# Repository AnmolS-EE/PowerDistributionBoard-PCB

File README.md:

# PowerDistributionBoard-PCB
A high-efficiency power distribution board (PDB) designed to convert a single DC input (24V/10A) into multiple regulated rails for laboratory and personal device charging. This project has a custom-designed buck converter stage, individual USB Power Delivery (PD) controllers, and an ESP32 for real-time telemetry and monitoring. It will be designed on a 4-layer PCB board designed in KiCad.
## Schematic
V1.0 of the schematic is complete. As seen by the image below, it is neatly organized into the four main compartments: MCU(Microcontroller), Power management, Power analysis and USB ports.

## PCB Design
The PCB design and layout is currently a work in progress. Schematic and simulations are being thoroughly verified first. 

## Simulations
### 24V to 5V Step-Down Buck Converter
**Objective:** Step down the 24V main system power to a highly stable 5V rail.

**Simulation Note (XL4016 vs. LT1074):** 
The XL4016 used in the KiCad schematic doesn’t have a public SPICE model, so I used the Analog Devices LT1074 to simulate the circuit and verify the LC filter design and transient behavior.
 
 Note: The feedback resistors in the simulation (1kΩ / 1.26kΩ) were chosen to match the LT1074’s 2.21V reference. On the actual PCB, I’m using (1kΩ / 3kΩ) based on the XL4016’s 1.25V reference.

**Simulation & Stress Test:**
I tested the regulator under a continuous 2.5A load (modeled as 2Ω) to check how the 47µH inductor and 470µF output capacitors perform. The capacitors were modeled with a realistic ESR of 50mΩ.

**1. Transient Startup & Output Ripple:**

The system ramps up to 5V in less than 2ms. Steady-state analysis at full load shows a peak-to-peak voltage ripple of roughly 40mV (under 1%), confirming the power delivery is quite clean.

### 3.3V Logic Rail
**Objective:** Provide a stable power rail for the ESP32-S3-WROOM-1 microcontroller and I2C peripherals using the AMS1117-3.3. 

**Simulation & Stress Test:**
To verify the stability of the AMS1117-3.3V LDO regulator, the circuit was simulated in LTspice. I applied a 5-ohm load to force a continuous 660mA draw which is double the worst-case scenario in real life.

**Conclusion:**
As shown in the transient analysis above, the input of 5V (blue line) is converted into 3.3V (green line). The total load of the 3.3V rail (red line) remains perfectly flat under a 660mA continuous load with no voltage drop. The schematic confirms the test parameters, proving the power delivery is efficient enough to power the microcontroller and other perpherals.

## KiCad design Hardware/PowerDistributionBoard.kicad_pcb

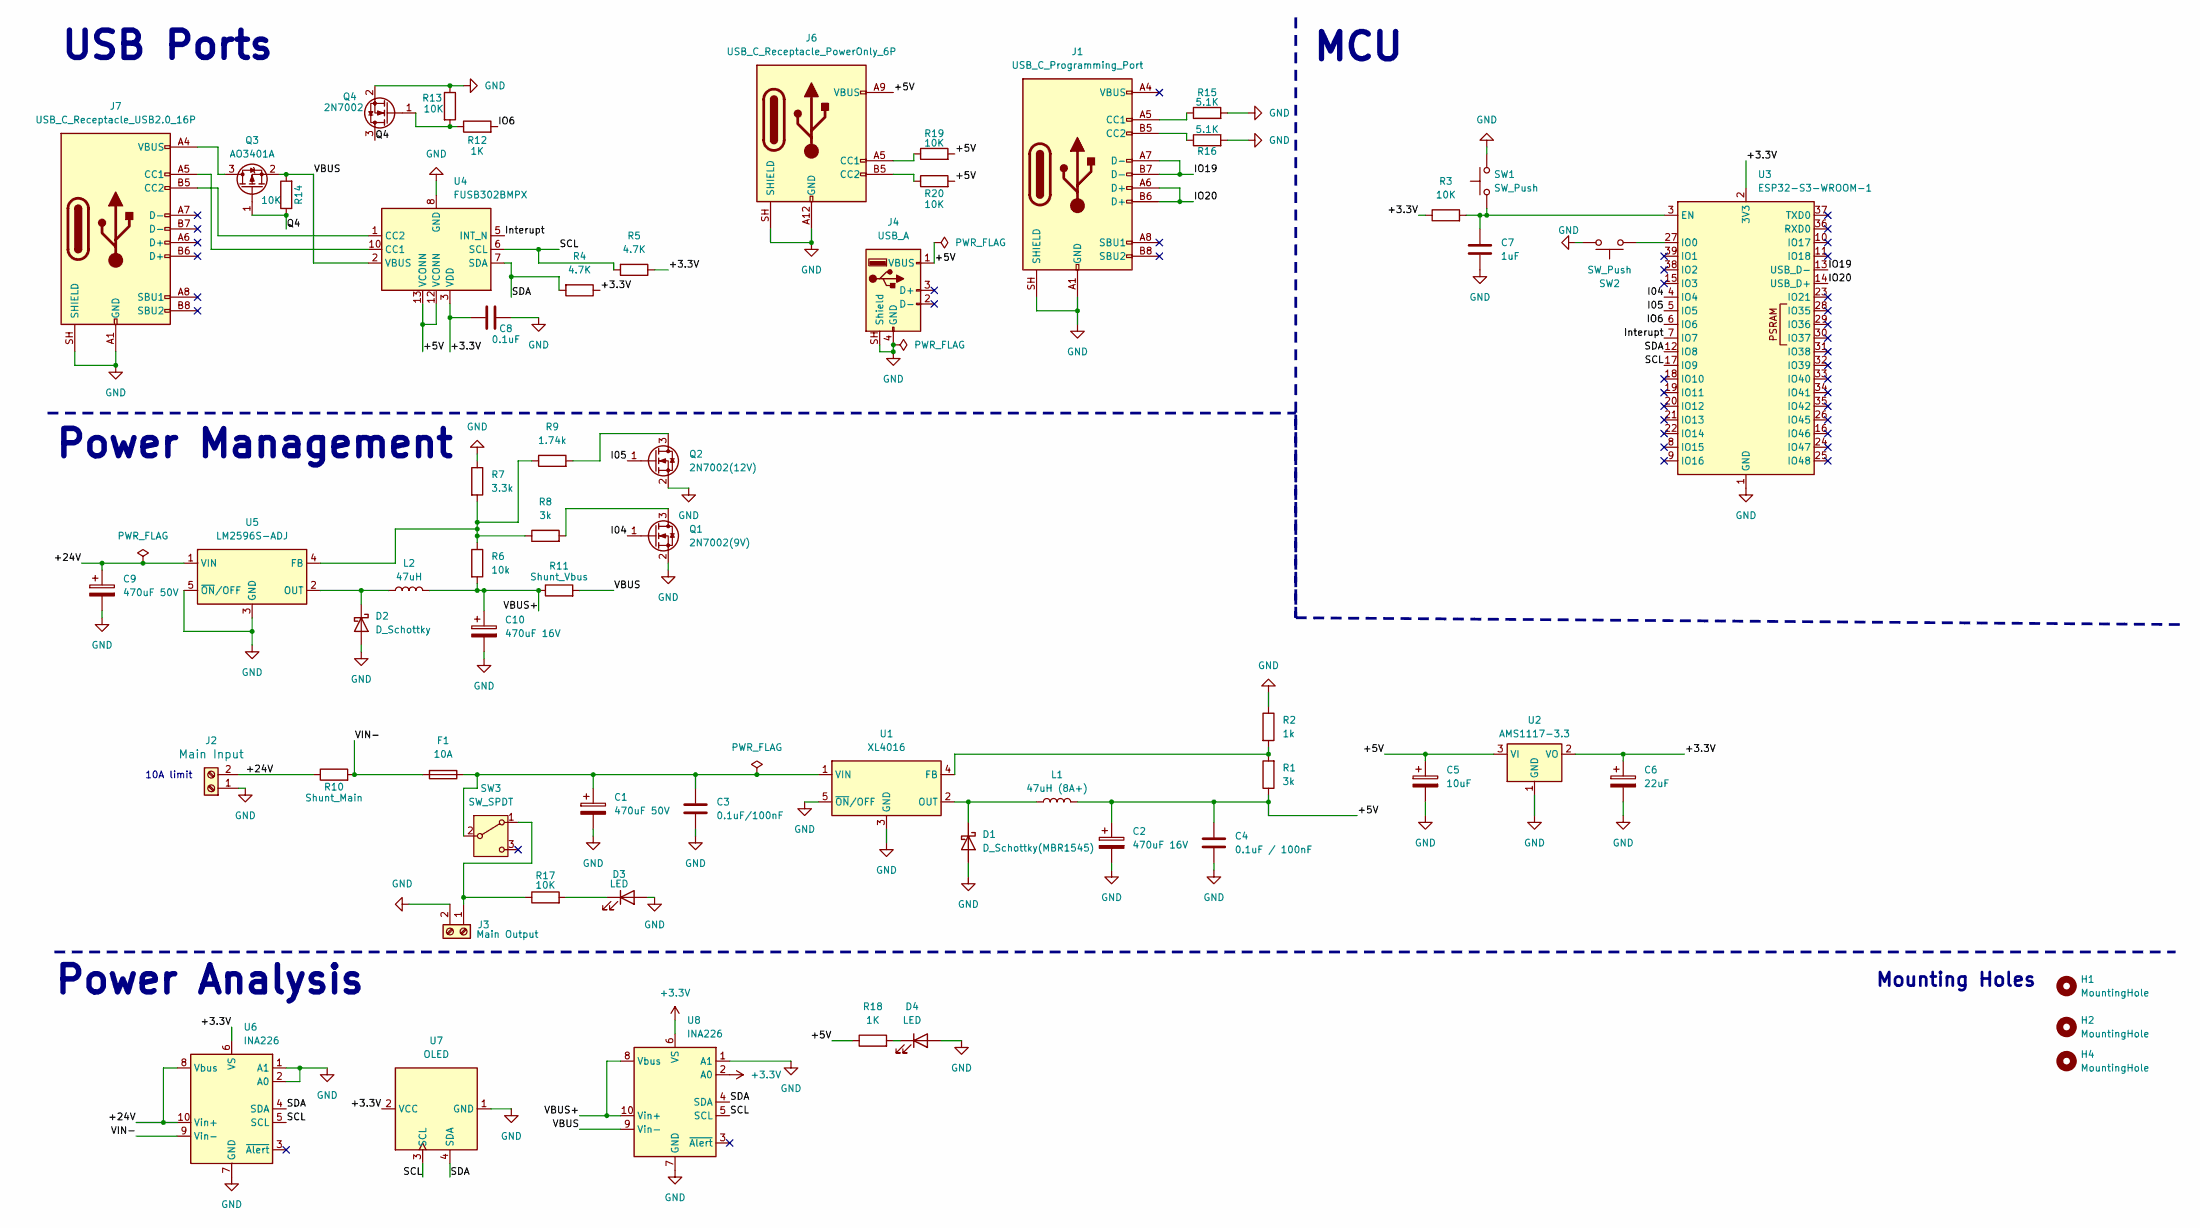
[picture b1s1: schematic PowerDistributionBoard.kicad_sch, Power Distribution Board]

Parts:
C1, C9: 470uF 50V; CP_Radial_D10.0mm_P5.00mm
C2, C10: 470uF 16V; CP_Radial_D8.0mm_P3.50mm
C3: 0.1uF/100nF; C_0805_2012Metric_Pad1.18x1.45mm_HandSolder
C4: 0.1uF / 100nF; C_0805_2012Metric_Pad1.18x1.45mm_HandSolder
C5: 10uF; CP_Radial_D5.0mm_P2.00mm
C6: 22uF; CP_Radial_D5.0mm_P2.00mm
C7: 1uF; C_0805_2012Metric_Pad1.18x1.45mm_HandSolder
C8: 0.1uF; C_0805_2012Metric_Pad1.18x1.45mm_HandSolder
D1: D_Schottky(MBR1545); TO-220-2_Vertical
D2: D_Schottky; D_SMC_Handsoldering
D3, D4: LED; LED_D3.0mm
F1: 10A; Fuseholder_Cylinder-5x20mm_Schurter_0031_8201_Horizontal_Op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
H1, H2, H4: MountingHole; MountingHole_3.2mm_M3
J1: USB_C_Programming_Port; USB_C_Receptacle_HRO_TYPE-C-31-M-12
J2: Main Input; TerminalBlock_Phoenix_MKDS-1,5-2-5.08_1x02_P5.08mm_Horizont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
J3: Main Output; TerminalBlock_Phoenix_MKDS-1,5-2-5.08_1x02_P5.08mm_Horizont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
J4: USB_A; USB_A_Molex_67643_Horizontal
J6: USB_C_Receptacle_PowerOnly_6P; USB_C_Receptacle_GCT_USB4125-xx-x_6P_TopMnt_Horizontal
J7: USB_C_Receptacle_USB2.0_16P; USB_C_Receptacle_HRO_TYPE-C-31-M-12
L1: 47uH (8A+); L_Toroid_Vertical_L24.6mm_W15.5mm_P11.44mm_Pulse_KM-4
L2: 47uH; L_12x12mm_H8mm
Q1: 2N7002(9V); SOT-23
Q2: 2N7002(12V); SOT-23
Q3: AO3401A; SOT-23
Q4: 2N7002; SOT-23
R1, R8: 3k; R_0805_2012Metric_Pad1.20x1.40mm_HandSolder
R2: 1k; R_0805_2012Metric_Pad1.20x1.40mm_HandSolder
R3, R13, R14, R17, R19, R20: 10K; R_0805_2012Metric_Pad1.20x1.40mm_HandSolder
R4, R5: 4.7K; R_0805_2012Metric_Pad1.20x1.40mm_HandSolder
R6: 10k; R_0805_2012Metric_Pad1.20x1.40mm_HandSolder
R7: 3.3k; R_0805_2012Metric_Pad1.20x1.40mm_HandSolder
R9: 1.74k; R_0805_2012Metric_Pad1.20x1.40mm_HandSolder
R10: Shunt_Main; R_2512_6332Metric_Pad1.40x3.35mm_HandSolder
R11: Shunt_Vbus; R_2512_6332Metric_Pad1.40x3.35mm_HandSolder
R12, R18: 1K; R_0805_2012Metric_Pad1.20x1.40mm_HandSolder
R15, R16: 5.1K; R_0805_2012Metric_Pad1.20x1.40mm_HandSolder
SW1, SW2: SW_Push; SW_PUSH_6x6mm_2Pin_P5.08mm
SW3: SW_SPDT; SW_Slide_SPDT_Straight_CK_OS102011MS2Q
U1: XL4016; TO-220-5_Vertical
U2: AMS1117-3.3; SOT-223-3_TabPin2
U3: ESP32-S3-WROOM-1
U4: FUSB302BMPX; WQFN-14-1EP_2.5x2.5mm_P0.5mm_EP1.45x1.45mm
U5: LM2596S-ADJ; TO-263-5_TabPin3
U6, U8: INA226; TSSOP-10_3x3mm_P0.5mm
U7: OLED; miniOLED

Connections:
+3.3V: C6.1, C8.1, R3.1, R4.1, R5.1, U2.2 (VO), U3.2 (3V3), U4.3 (VDD), U4.4 (VDD), U6.6 (VS), U7.2 (VCC), U8.2 (A0), U8.6 (VS)
/+5V: C2.1, C4.1, C5.1, J4.1 (VBUS), J6.A9 (VBUS), J6.B9 (VBUS), L1.2, R1.1, R18.1, R19.2, R20.2, U2.3 (VI), U4.12 (VCONN), U4.13 (VCONN)
/+24V: C9.1, J2.2, R10.1, U5.1 (VIN), U6.8 (Vbus), U6.10 (Vin+)
/I04: Q1.1 (G), U3.4 (IO4)
/I05: Q2.1 (G), U3.5 (IO5)
/IO6: R12.2, U3.6 (IO6)
/IO19: J1.A7 (D-), J1.B7 (D-), U3.13 (USB_D-)
/IO20: J1.A6 (D+), J1.B6 (D+), U3.14 (USB_D+)
/Interupt: U3.7 (IO7), U4.5 (INT_N)
/Q4: Q3.1 (G), Q4.3 (D), R14.1
/SCL: R5.2, U3.17 (IO9), U4.6 (SCL), U6.5 (SCL), U7.3 (SCL), U8.5 (SCL)
/SDA: R4.2, U3.12 (IO8), U4.7 (SDA), U6.4 (SDA), U7.4 (SDA), U8.4 (SDA)
/VBUS: Q3.2 (S), R11.2, R14.2, U4.2 (VBUS), U8.9 (Vin-)
/VBUS+: C10.1, L2.2, R6.2, R11.1, U8.8 (Vbus), U8.10 (Vin+)
/VIN-: F1.2, R10.2, U6.9 (Vin-)
GND: C1.2, C2.2, C3.2, C4.2, C5.2, C6.2, C7.2, C8.2, C9.2, C10.2, D1.2 (A), D2.2 (A), D3.2 (A), D4.2 (A), J1.A1 (GND), J1.A12 (GND), J1.B1 (GND), J1.B12 (GND), J1.SH (SHIELD), J2.1, J3.2, J4.4 (GND), J4.SH (Shield), J6.A12 (GND), J6.B12 (GND), J6.SH (SHIELD), J7.A1 (GND), J7.A12 (GND), J7.B1 (GND), J7.B12 (GND), J7.SH (SHIELD), Q1.2 (S), Q2.2 (S), Q4.2 (S), R2.1, R7.1, R13.1, R15.2, R16.2, SW1.2, SW2.2, U1.3 (GND), U1.5 (~ON/OFF), U2.1 (GND), U3.1 (GND), U3.40 (GND), U3.41 (GND), U4.8 (GND), U4.9 (GND), U4.15 (GND), U5.3 (GND), U5.5 (~ON/OFF), U6.1 (A1), U6.2 (A0), U6.7 (GND), U7.1 (GND), U8.1 (A1), U8.7 (GND)
unnamed: D1.1 (K), L1.1, U1.2 (OUT)
unnamed: D2.1 (K), L2.1, U5.2 (OUT)
unnamed: D3.1 (K), R17.2
unnamed: D4.1 (K), R18.2
unnamed: J1.A5 (CC1), R15.1
unnamed: J1.B5 (CC2), R16.1
unnamed: J3.1, R17.1, SW3.1 (A)
unnamed: J6.A5 (CC1), R19.1
unnamed: J6.B5 (CC2), R20.1
unnamed: J7.A5 (CC1), U4.10 (CC1), U4.11 (CC1)
unnamed: J7.B5 (CC2), U4.1 (CC2), U4.14 (CC2)
unnamed: Q1.3 (D), R8.2
unnamed: Q2.3 (D), R9.2
unnamed: J7.A4 (VBUS), J7.A9 (VBUS), J7.B4 (VBUS), J7.B9 (VBUS), Q3.3 (D)
unnamed: Q4.1 (G), R12.1, R13.2
unnamed: C1.1, C3.1, F1.1, SW3.2 (B), U1.1 (VIN)
unnamed: R1.2, R2.2, U1.4 (FB)
unnamed: C7.1, R3.2, SW1.1, U3.3 (EN)
unnamed: SW2.1, U3.27 (IO0)
unnamed: R6.1, R7.2, R8.1, R9.1, U5.4 (FB)

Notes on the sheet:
Mounting Holes
MCU
USB Ports
Power Management
Power Analysis
10A limit

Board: 4 copper layers, 61 parts (0 on the bottom side), 36 nets, no tracks yet.

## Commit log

2026-04-30 Create .gitignore for KiCad project
    Add .gitignore for KiCad project files and temporary files.
2026-04-30 Inital KiCad files upload
2026-05-01 Upgraded the schematic
2026-05-01 Updated Schematic
2026-05-02 V1.0 of Schematic is complete
2026-05-02 Update .gitignore to include LTspice files
    Add rules to ignore LTspice simulation files and logs.
2026-05-02 V1.0 of Schematic is complete.
2026-05-03 Added simulations
2026-05-03 Finished 3 main simulations
2026-05-05 Uploading V1.0 Schematic pdf
2026-05-05 Expand README with project details and simulations
    Added detailed sections on schematic, PCB design, and simulations for the power distribution board project.
